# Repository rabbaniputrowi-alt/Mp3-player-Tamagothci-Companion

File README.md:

# MP3 Player + Tamagotchi Companion
A MP3 Player that lives under a star-shaped casing and displays a spinning album of the track playing! whilst also a Tamagotchi pet that lives in a round screen and reacts to button interactions, tilt, or even when you shake it.

## Why I built it?
Music is everything to me, it helps me focus and soothes my mind, however my school confiscated our phones making it hard for me to focus in school. Therefore i took it upon myself to create and design my very own mp3 player. Inspired by Lil guy from starboy, I then created my own version of a Tamagotchi pet that uses the faces of bees in a roblox game called Bee Swarm Simulator as the Tamagotchi pet. 

## Inspired by

- **Bee Swarm Simulator (Gifted bees).** The pet's faces are the bees from this Roblox game, and the gifted star is where the star shape comes from.
- **The Lil Guy from Starboy.** A small star-shaped companion you hold in your hand, which is what I wanted to build for real.

| Bee Swarm Simulator, gifted stars | Starboy Lil Guy |
|---|---|
|  |  |

Both images are third-party material, used here only to show the inspiration. They belong to their respective owners.

## Characters used in this project

The pet's faces are bees from Bee Swarm Simulator, and each one is used for a different reaction. Tutorial Terry, the dancing penguin, is the odd one out and comes from BloxTales.

<table>
<tr><td align="center"><br>Rest face: blink and look around</td><td align="center"><br>Affection wink (NEXT)</td><td align="center"><br>Bubble face, a rare idle</td></tr>
<tr><td align="center"><br>Music spin (MENU transition)</td><td align="center"><br>Scared and dizzy when shaken</td><td align="center"><br>Tutorial Terry (BloxTales), PLAY</td></tr>
</table>

These are third-party characters, shown only to document what the animations are based on. They belong to their respective owners.

## Features
- Plays MP3s from a microSD card, organised as playlists (one folder per album)
- Album cover rendered as a spinning disc, full screen, with spin-up and spin-down easing
- Playlist and track chooser over a blurred backdrop of the album art
- Animated pet with idle clips, interactive clips and a "face on a ball" view that follows the tilt of the device
- Shake it and the pet gets dizzy
- A Tutorial Terry (BloxTales) dance mode (press PLAY in the pet view)
- Autoplay: the next track starts by itself when one ends
- 3.5 mm headphone output
- USB-C charging for a 1200 mAh LiPo (on the PCB design)

### The pet

| Blink | Wink | Tilt follow | Shake to dizzy |
|---|---|---|---|
|  |  |  |  |

## Hardware

| Part | Notes |
|---|---|
| MCU | Waveshare RP2040-Zero |
| Display | GC9A01 1.28" round TFT, 240x240, SPI |
| Audio | DFPlayer Mini (clone) with microSD slot |
| Motion | MPU6050 (GY-521) accelerometer and gyro |
| Output | PJ-307 3.5 mm TRS jack |
| Input | 4 tactile buttons |
| Power | 3.7 V 1200 mAh LiPo (40x30x10 mm), on-board TP4056 charger, DW01A + FS8205A protection, SS14 into VSYS, USB-C |

Parts list: [BOM.csv](BOM.csv). Pricing notes and open questions: [docs/BOM_NOTES.md](docs/BOM_NOTES.md).

The priced lines add up to $59.20 for one device, under the $120 cap. Four lines are unpriced (the LiPo, PCB shipping, case filament, and order shipping and import duties), so the cap check is approximate. Several priced lines are substitutes or upper bounds, which BOM_NOTES.md lists.

### Pinout

| Signal | RP2040-Zero pin |
|---|---|
| Display SCK (labelled SCL on the module) | GP14 |
| Display MOSI (labelled SDA on the module) | GP15 |
| Display CS | GP6 |
| Display DC | GP7 |
| Display RST | GP8 |
| DFPlayer RX (via 1k resistor) | GP28 (MCU TX) |
| DFPlayer TX | GP29 (MCU RX) |
| DFPlayer BUSY (via 10k resistor, used for autoplay) | GP27 |
| MPU6050 SDA | GP4 |
| MPU6050 SCL | GP5 |
| Button PREV | GP0 |
| Button PLAY | GP1 |
| Button NEXT | GP2 |
| Button MENU | GP3 |
| Battery sense (ADC, through a 100k/100k divider) | GP26 |
| Battery in | VSYS (not 3V3) |

The display module borrows I2C names for its SPI pins, so SCL is the clock and SDA is the data line. Buttons are wired to ground and use `INPUT_PULLUP`, so they read low when pressed. GP9 to GP13 are not reachable on this board and are not used.

On the PCB design the DFPlayer VCC is on VSYS. The old breadboard used the 3.3 V rail. The full wiring reference for both is in [wiring.md](wiring.md).

## Hardware files

Only the finished design files are kept in the repo:

- `PCB/` is the KiCad project for the carrier board: `stardance_pcb.kicad_pro` (open this), `stardance_pcb.kicad_sch` (schematic) and `stardance_pcb.kicad_pcb` (board).
- `CAD/` has case v4 as STEP files: `stardance_case_v4.step` (the whole case), `stardance_v4_front_shell.step` and `stardance_v4_back_shell.step`. Export STL from these for printing.

Previews of both are in "PCB and case" below. The generator scripts, PDFs, custom libraries and older revisions are not included.

## Repository layout

```
firmware/          the firmware sketch (firmware.ino and all .cpp/.h files, flat)
tools/
  Spinning Disc/    album art and track name generators
  Pet_Pipeline/     pet animation generator and previewer
  UI_Fonts/         chooser font generator and the font files
  previews/         pet preview gifs and contact sheets
docs/               BOM notes, merge plan, TFT_eSPI setup example, shipping checklist, images/ for the README
PCB/                KiCad project (.kicad_pro, .kicad_sch, .kicad_pcb)
CAD/                case v4 STEP files
Archive/            old code, kept for reference only
BOM.csv             bill of materials
wiring.md           wiring reference (breadboard and PCB)
```

## Building the firmware

Tested with arduino-pico 6.3.1.

1. Install the Arduino IDE and the [arduino-pico](https://github.com/earlephilhower/arduino-pico) core by Earle Philhower (6.3.1).
2. Board: `Waveshare RP2040 Zero`. Flash Size: `2MB (no FS)`.
3. Install the libraries:
   - `TFT_eSPI` 2.5.43
   - `DFRobotDFPlayerMini` 1.0.6
4. Edit `User_Setup.h` in `Documents/Arduino/libraries/TFT_eSPI`. [docs/User_Setup.example.h](docs/User_Setup.example.h) is a starting point. It is a reconstruction from the project notes, not a copy of the working file, and it leaves SPI_FREQUENCY open. The settings that matter:
   ```c
   #define GC9A01_DRIVER
   #define TFT_SPI_PORT 1
   #define TFT_SCLK 14
   #define TFT_MOSI 15
   #define TFT_CS   6
   #define TFT_DC   7
   #define TFT_RST  8
   ```
5. Open `firmware/firmware.ino` and upload.

If a change to `User_Setup.h` does not seem to take effect, delete the cached build in `AppData\Local\arduino\sketches\` and compile again.

Python is only needed to regenerate the album, track, pet and font data: `pip install pillow numpy imageio-ffmpeg` (and `fonttools brotli` for the fonts).

## Preparing the SD card

The DFPlayer only understands exact names:

```
01/001.mp3
01/002.mp3
02/001.mp3
...
```

Folders `01` to `99`, files `001.mp3` to `255.mp3`, no extra text in either name. Each folder is one playlist. The firmware currently knows seven albums, folders `01` to `07`. The music itself is not in this repo.

## Adding an album

Run the generators from the folder that holds their json, with `--out` pointing at the `firmware` sketch folder.

1. Add the cover image and an entry in `albums.json`, then run
   `python build_albums.py --manifest albums.json --out <sketch>`
2. Add a row for the new folder to `PLAYLIST_ART[]` in `playlist_art.cpp`
3. Add the folder to `tracks.json`, then run
   `python build_tracks.py --manifest tracks.json --out <sketch>`
   (or add `--scan <SD card drive>` to read titles off the card)

If you skip step 2 the album never shows up in the chooser.

## Controls

Each view owns PREV, PLAY and NEXT. In the pet view the music is not touched.

| Button | Disc view | Pet view |
|---|---|---|
| PREV | previous track | pet winks |
| PLAY | play/pause | starts or stops the Tutorial Terry dance |
| NEXT | next track | affection wink |
| MENU (short) | open the playlist chooser | open the playlist chooser |
| MENU (hold) | switch to pet view | switch to disc view |

In the chooser, PREV and NEXT turn the list, PLAY opens a playlist or plays a track, and MENU goes back. When a track ends, the next one in the playlist starts by itself (autoplay).

The device boots into the pet view.

## PCB and case

The carrier PCB (version 2) is a 2-layer, 1.2 mm board that holds the RP2040-Zero, DFPlayer, MPU6050, buttons, jack and the charging circuit, with the battery underneath. The case is 3D printed and closes with four M2 screws into heat-set inserts. The KiCad project is in `PCB/` and the case v4 files are in `CAD/` (see "Hardware files").

### PCB

| Front | Back |
|---|---|
|  |  |

### Case

## Credits

- [TFT_eSPI](https://github.com/Bodmer/TFT_eSPI) by Bodmer
- [DFRobotDFPlayerMini](https://github.com/DFRobot/DFRobotDFPlayerMini) by DFRobot
- [arduino-pico](https://github.com/earlephilhower/arduino-pico) by Earle Philhower
- Lora and DM Sans fonts, SIL Open Font License (license texts in `tools/UI_Fonts/fonts/`: [OFL-Lora.txt](tools/UI_Fonts/fonts/OFL-Lora.txt), [OFL-DMSans.txt](tools/UI_Fonts/fonts/OFL-DMSans.txt))
- The pet animations are my own clips. Tutorial Terry, the dancing penguin, is a BloxTales character, credited here as that and to be replaced before redistribution.
- Album covers: third-party artwork, placeholders (see Known limitations).

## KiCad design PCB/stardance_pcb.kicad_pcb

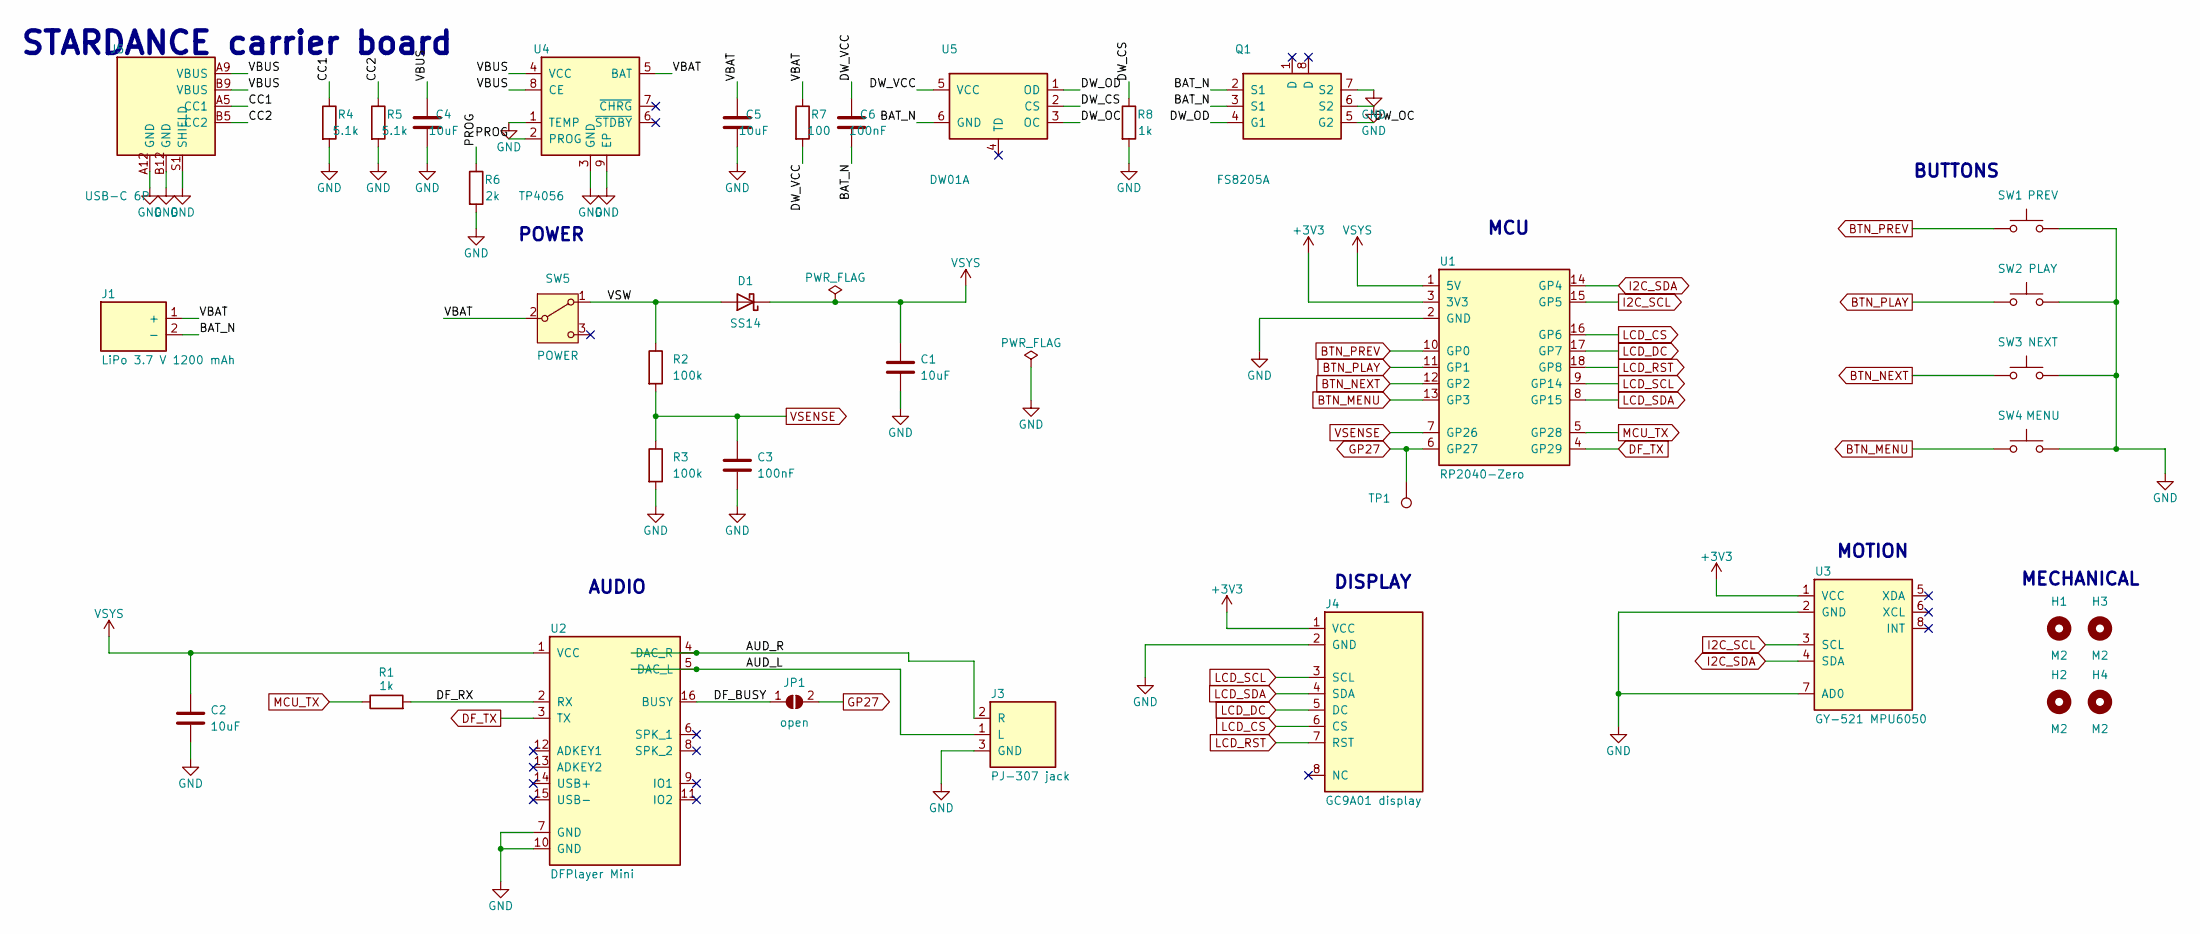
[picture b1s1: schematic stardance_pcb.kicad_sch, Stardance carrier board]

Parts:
C1, C2, C4, C5: 10uF; C_0805_2012Metric_Pad1.18x1.45mm_HandSolder
C3, C6: 100nF; C_0805_2012Metric_Pad1.18x1.45mm_HandSolder
D1: SS14; D_SMA
H1, H2, H3, H4: M2; MountingHole_2.2mm_M2
J1: LiPo 3.7 V 1200 mAh; SolderWire-0.5sqmm_1x02_P4.6mm_D0.9mm_OD2.1mm
J3: PJ-307 jack; PinHeader_1x03_P2.54mm_Vertical
J4: GC9A01 display; PinHeader_2x04_P2.00mm_Vertical
J5: USB-C 6P; USB_C_Receptacle_GCT_USB4125-xx-x_6P_TopMnt_Horizontal
JP1: open; SolderJumper-2_P1.3mm_Open_RoundedPad1.0x1.5mm
Q1: FS8205A; TSSOP-8_4.4x3mm_P0.65mm
R1, R8: 1k; R_0805_2012Metric_Pad1.20x1.40mm_HandSolder
R2, R3: 100k; R_0805_2012Metric_Pad1.20x1.40mm_HandSolder
R4, R5: 5.1k; R_0805_2012Metric_Pad1.20x1.40mm_HandSolder
R6: 2k; R_0805_2012Metric_Pad1.20x1.40mm_HandSolder
R7: 100; R_0805_2012Metric_Pad1.20x1.40mm_HandSolder
SW1: PREV; SW_Tactile_SPST_Angled_PTS645Vx58-2LFS
SW2: PLAY; SW_PUSH_6mm
SW3: NEXT; SW_Tactile_SPST_Angled_PTS645Vx58-2LFS
SW4: MENU; SW_Tactile_SPST_Angled_PTS645Vx58-2LFS
SW5: POWER; SW_Slide_SPDT_Angled_CK_OS102011MA1Q
TP1: GP27; TestPoint_Pad_D1.5mm
U1: RP2040-Zero; RP2040_Zero
U2: DFPlayer Mini; DFPlayer_Mini
U3: GY-521 MPU6050; GY521_MPU6050
U4: TP4056; SOIC-8-1EP_3.9x4.9mm_P1.27mm_EP2.41x3.3mm
U5: DW01A; SOT-23-6_Handsoldering

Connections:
+3V3: J4.1 (VCC), U1.3 (3V3), U3.1 (VCC)
/AUD_L: J3.1 (L), U2.5 (DAC_L)
/AUD_R: J3.2 (R), U2.4 (DAC_R)
/BAT_N: C6.2, J1.2 (-), Q1.2 (S1), Q1.3 (S1), U5.6 (GND)
/CC1: J5.A5 (CC1), R4.1
/CC2: J5.B5 (CC2), R5.1
/DF_BUSY: JP1.1 (A), U2.16 (BUSY)
/DF_RX: R1.2, U2.2 (RX)
/DW_CS: R8.1, U5.2 (CS)
/DW_OC: Q1.5 (G2), U5.3 (OC)
/DW_OD: Q1.4 (G1), U5.1 (OD)
/DW_VCC: C6.1, R7.2, U5.5 (VCC)
/PROG: R6.1, U4.2 (PROG)
/VBAT: C5.1, J1.1 (+), R7.1, SW5.2 (B), U4.5 (BAT)
/VBUS: C4.1, J5.A9 (VBUS), J5.B9 (VBUS), U4.4 (VCC), U4.8 (CE)
/VSW: D1.2 (A), R2.1, SW5.1 (A)
BTN_MENU: SW4.1, U1.13 (GP3)
BTN_NEXT: SW3.1, U1.12 (GP2)
BTN_PLAY: SW2.1, U1.11 (GP1)
BTN_PREV: SW1.1, U1.10 (GP0)
DF_TX: U1.4 (GP29), U2.3 (TX)
GND: C1.2, C2.2, C3.2, C4.2, C5.2, J3.3 (GND), J4.2 (GND), J5.A12 (GND), J5.B12 (GND), J5.S1 (SHIELD), Q1.6 (S2), Q1.7 (S2), R3.2, R4.2, R5.2, R6.2, R8.2, SW1.2, SW2.2, SW3.2, SW4.2, U1.2 (GND), U2.7 (GND), U2.10 (GND), U3.2 (GND), U3.7 (AD0), U4.1 (TEMP), U4.3 (GND), U4.9 (EP)
GP27: JP1.2 (B), TP1.1, U1.6 (GP27)
I2C_SCL: U1.15 (GP5), U3.3 (SCL)
I2C_SDA: U1.14 (GP4), U3.4 (SDA)
LCD_CS: J4.6 (CS), U1.16 (GP6)
LCD_DC: J4.5 (DC), U1.17 (GP7)
LCD_RST: J4.7 (RST), U1.18 (GP8)
LCD_SCL: J4.3 (SCL), U1.9 (GP14)
LCD_SDA: J4.4 (SDA), U1.8 (GP15)
MCU_TX: R1.1, U1.5 (GP28)
VSENSE: C3.1, R2.2, R3.1, U1.7 (GP26)
VSYS: C1.1, C2.1, D1.1 (K), U1.1 (5V), U2.1 (VCC)

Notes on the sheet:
MECHANICAL
MCU
POWER
DISPLAY
MOTION
STARDANCE carrier board
AUDIO
BUTTONS

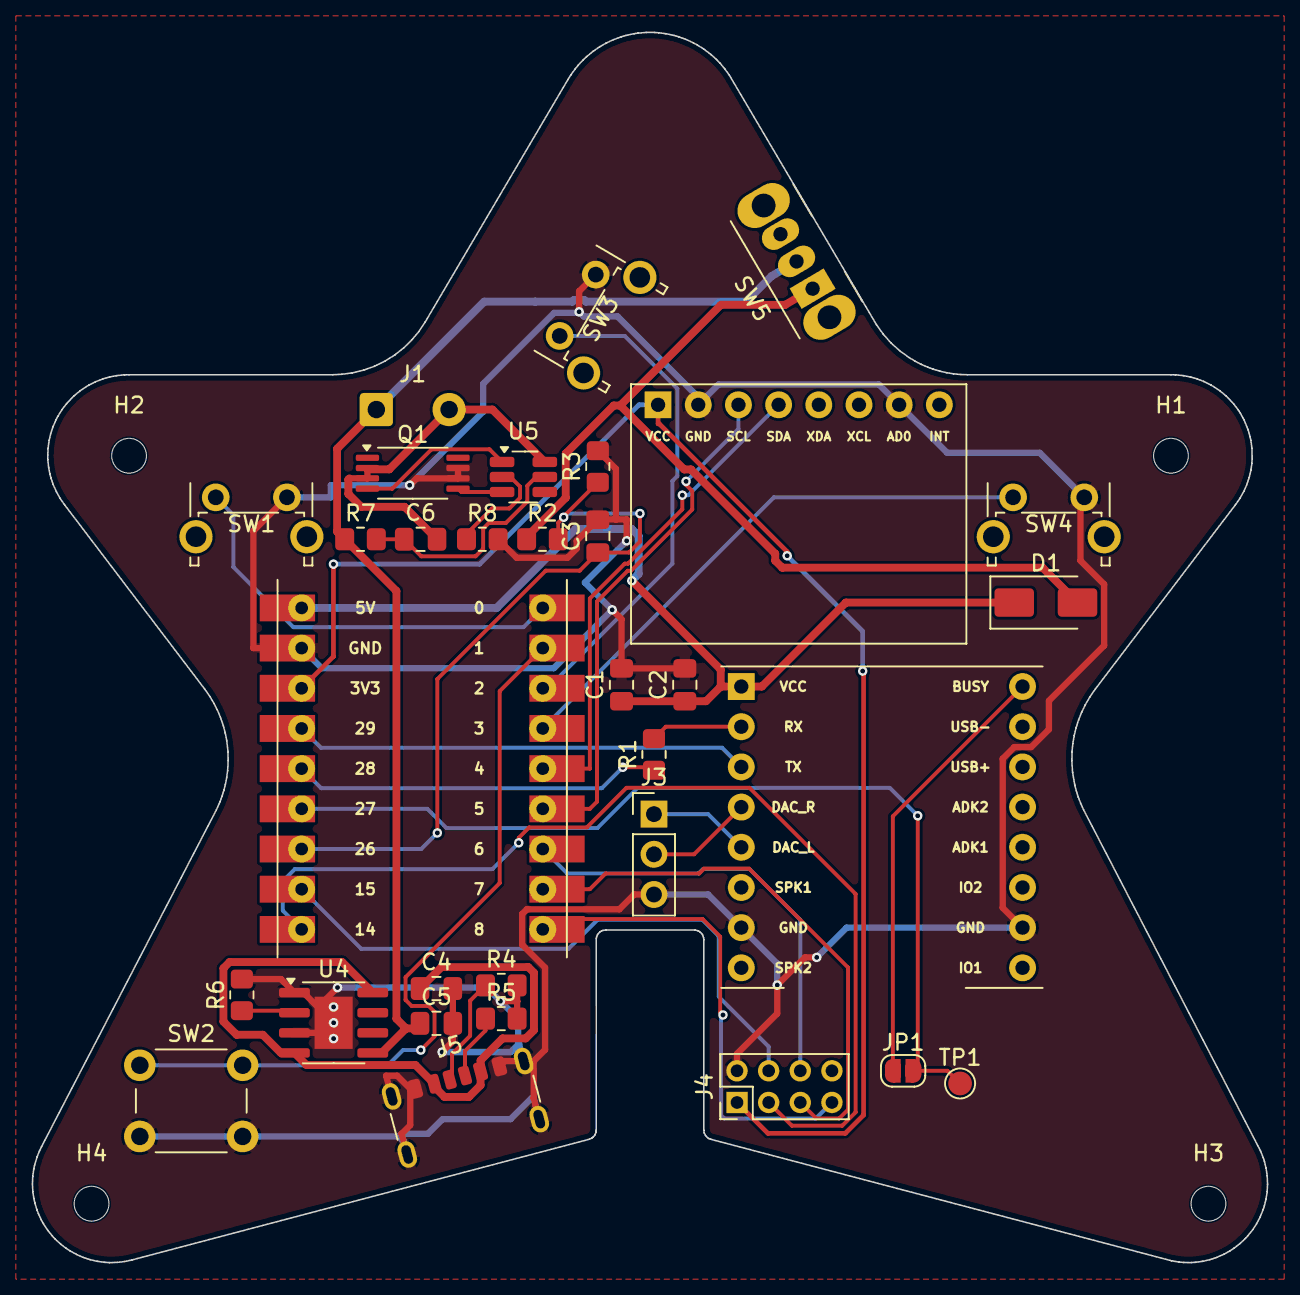
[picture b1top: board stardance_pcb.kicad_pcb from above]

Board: 2 copper layers, 78.1 x 77.8 mm, 36 parts (0 on the bottom side), 33 nets.

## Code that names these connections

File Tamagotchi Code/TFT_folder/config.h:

#pragma once
#include <stdint.h>

#define TFT_SCLK_PIN   14
#define TFT_MOSI_PIN   15
#define TFT_CS_PIN      6
#define TFT_DC_PIN      7
#define TFT_RST_PIN     8

#define DFPLAYER_TX_PIN  28
#define DFPLAYER_RX_PIN  29

#define MPU6050_SDA_PIN   4
#define MPU6050_SCL_PIN   5

#define PIN_BTN_PREV   0   // playing: previous | select: scroll up
#define PIN_BTN_PLAY   1   // playing: play/pause | select: confirm
#define PIN_BTN_NEXT   2   // playing: next | select: scroll down
#define PIN_BTN_MENU   3   // playing: open chooser | select: back

#define SCREEN_W      240
#define SCREEN_H      240
#define DISC_CX       120
#define DISC_CY       120
#define DISC_R        118   // slightly inside 240px edge — keeps source index in range

#define ART_W         240              // source art edge, square
#define ART_PIXELS    (ART_W * ART_W)  // 57600 — indexed pixels, 1 byte each
#define PALETTE_SIZE  256

#define BAND_H         48              // 240 / 5 bands per frame
#define BAND_PIXELS   (SCREEN_W * BAND_H)
#define NUM_BANDS     (SCREEN_H / BAND_H)

enum class AppState : uint8_t {
  PLAYING = 0,
  PLAYLIST_SELECT,
  TRACK_SELECT
};

#define ROW_PITCH      43
#define BAND_Y0        98
#define BAND_Y1       142
#define VISIBLE_SPAN    2
#define TEXT_MARGIN     8
#define GLYPH_HALF     22
#define SLIDE_MS      200
#define MAX_PLAYLISTS   8

#define COL_BAND   0xEF7D
#define COL_SEL    0x0000
#define COL_SHADOW 0x0000

#define TEXT_NEAR       205
#define TEXT_FAR        140

#define BG_CELL           4
#define BG_BLUR_PASSES    1
#define BG_TARGET_LUMA   84
#define BG_DIM          200
#define BG_SATURATION   384
